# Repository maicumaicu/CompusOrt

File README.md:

# CompusOrt

Este es un proyecto para armar un carro con sensores para detectar si las computadoras estan

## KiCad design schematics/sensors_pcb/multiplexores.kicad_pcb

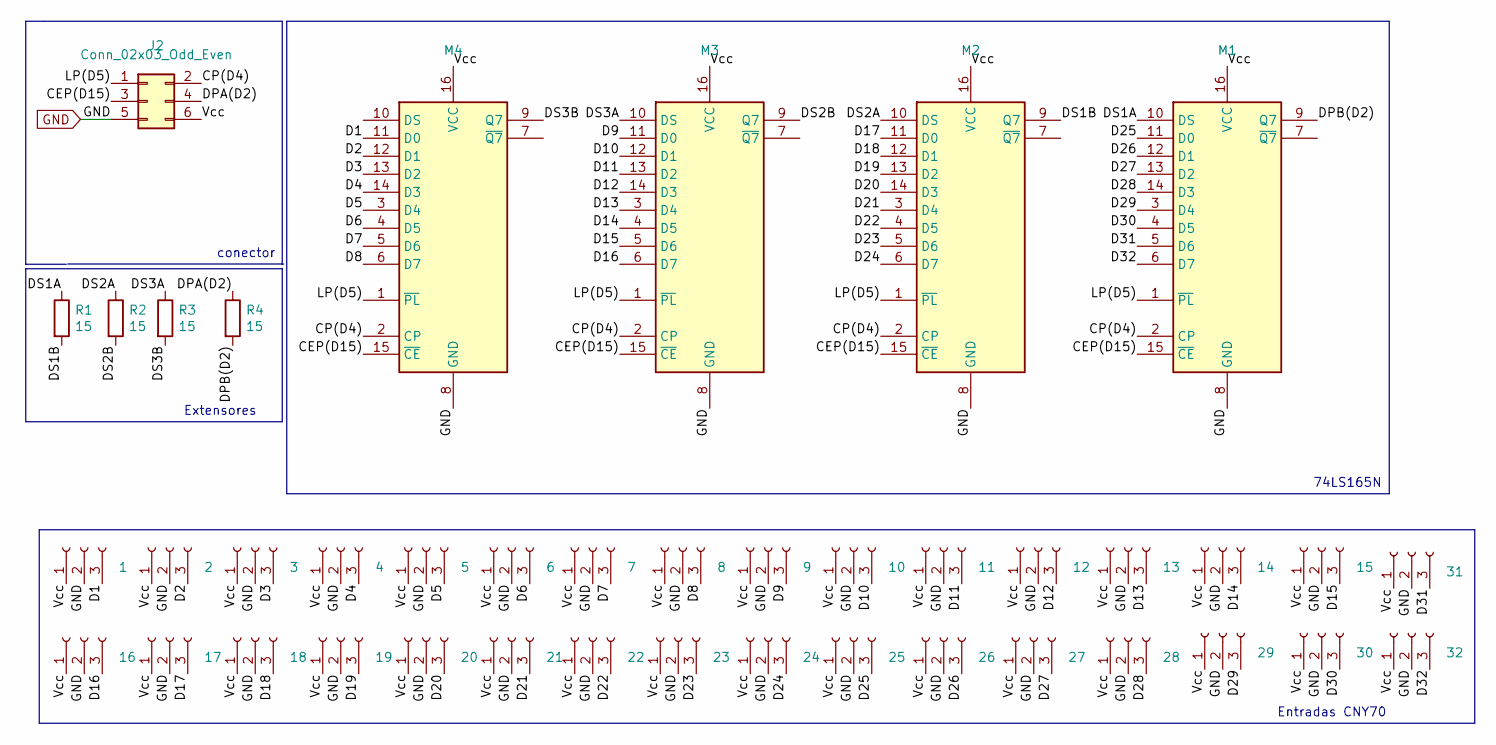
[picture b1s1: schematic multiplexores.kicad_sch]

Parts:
Conn1: 1; PinSocket_1x03_P2.54mm_Vertical
Conn2: 2; PinSocket_1x03_P2.54mm_Vertical
Conn3: 3; PinSocket_1x03_P2.54mm_Vertical
Conn5: 5; PinSocket_1x03_P2.54mm_Vertical
Conn6: 6; PinSocket_1x03_P2.54mm_Vertical
Conn8: 8; PinSocket_1x03_P2.54mm_Vertical
Conn9: 9; PinSocket_1x03_P2.54mm_Vertical
Conn10: 10; PinSocket_1x03_P2.54mm_Vertical
Conn11: 11; PinSocket_1x03_P2.54mm_Vertical
Conn12: 12; PinSocket_1x03_P2.54mm_Vertical
Conn13: 13; PinSocket_1x03_P2.54mm_Vertical
Conn14: 14; PinSocket_1x03_P2.54mm_Vertical
Conn15: 15; PinSocket_1x03_P2.54mm_Vertical
Conn16: 16; PinSocket_1x03_P2.54mm_Vertical
Conn17: 17; PinSocket_1x03_P2.54mm_Vertical
Conn18: 18; PinSocket_1x03_P2.54mm_Vertical
Conn19: 19; PinSocket_1x03_P2.54mm_Vertical
Conn20: 20; PinSocket_1x03_P2.54mm_Vertical
Conn21: 21; PinSocket_1x03_P2.54mm_Vertical
Conn22: 22; PinSocket_1x03_P2.54mm_Vertical
Conn23: 23; PinSocket_1x03_P2.54mm_Vertical
Conn24: 24; PinSocket_1x03_P2.54mm_Vertical
Conn25: 25; PinSocket_1x03_P2.54mm_Vertical
Conn26: 26; PinSocket_1x03_P2.54mm_Vertical
Conn27: 27; PinSocket_1x03_P2.54mm_Vertical
Conn28: 28; PinSocket_1x03_P2.54mm_Vertical
Conn29: 29; PinSocket_1x03_P2.54mm_Vertical
Conn30: 30; PinSocket_1x03_P2.54mm_Vertical
Conn31: 31; PinSocket_1x03_P2.54mm_Vertical
Conn32: 32; PinSocket_1x03_P2.54mm_Vertical
J2: Conn_02x03_Odd_Even; IDC-Header_2x03_P2.54mm_Vertical
M1, M2, M3, M4: 74LS165; DIP-16_W7.62mm_Socket_LongPads
R1, R2, R3, R4: 15; extensor 15mm
conn4: 4; PinSocket_1x03_P2.54mm_Vertical
conn7: 7; PinSocket_1x03_P2.54mm_Vertical

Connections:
/CEP(D15): J2.3, M1.15 (~CE), M2.15 (~CE), M3.15 (~CE), M4.15 (~CE)
/CP(D4): J2.2, M1.2 (CP), M2.2 (CP), M3.2 (CP), M4.2 (CP)
/D1: Conn1.3, M4.11 (D0)
/D2: Conn2.3, M4.12 (D1)
/D3: Conn3.3, M4.13 (D2)
/D4: M4.14 (D3), conn4.3
/D5: Conn5.3, M4.3 (D4)
/D6: Conn6.3, M4.4 (D5)
/D7: M4.5 (D6), conn7.3
/D8: Conn8.3, M4.6 (D7)
/D9: Conn9.3, M3.11 (D0)
/D10: Conn10.3, M3.12 (D1)
/D11: Conn11.3, M3.13 (D2)
/D12: Conn12.3, M3.14 (D3)
/D13: Conn13.3, M3.3 (D4)
/D14: Conn14.3, M3.4 (D5)
/D15: Conn15.3, M3.5 (D6)
/D16: Conn16.3, M3.6 (D7)
/D17: Conn17.3, M2.11 (D0)
/D18: Conn18.3, M2.12 (D1)
/D19: Conn19.3, M2.13 (D2)
/D20: Conn20.3, M2.14 (D3)
/D21: Conn21.3, M2.3 (D4)
/D22: Conn22.3, M2.4 (D5)
/D23: Conn23.3, M2.5 (D6)
/D24: Conn24.3, M2.6 (D7)
/D25: Conn25.3, M1.11 (D0)
/D26: Conn26.3, M1.12 (D1)
/D27: Conn27.3, M1.13 (D2)
/D28: Conn28.3, M1.14 (D3)
/D29: Conn29.3, M1.3 (D4)
/D30: Conn30.3, M1.4 (D5)
/D31: Conn31.3, M1.5 (D6)
/D32: Conn32.3, M1.6 (D7)
/DPA(D2): J2.4, R4.1
/DPB(D2): M1.9 (Q7), R4.2
/DS1A: M1.10 (DS), R1.1
/DS1B: M2.9 (Q7), R1.2
/DS2A: M2.10 (DS), R2.1
/DS2B: M3.9 (Q7), R2.2
/DS3A: M3.10 (DS), R3.1
/DS3B: M4.9 (Q7), R3.2
/LP(D5): J2.1, M1.1 (~PL), M2.1 (~PL), M3.1 (~PL), M4.1 (~PL)
/Vcc: Conn1.1, Conn2.1, Conn3.1, Conn5.1, Conn6.1, Conn8.1, Conn9.1, Conn10.1, Conn11.1, Conn12.1, Conn13.1, Conn14.1, Conn15.1, Conn16.1, Conn17.1, Conn18.1, Conn19.1, Conn20.1, Conn21.1, Conn22.1, Conn23.1, Conn24.1, Conn25.1, Conn26.1, Conn27.1, Conn28.1, Conn29.1, Conn30.1, Conn31.1, Conn32.1, J2.6, M1.16 (VCC), M2.16 (VCC), M3.16 (VCC), M4.16 (VCC), conn4.1, conn7.1
GND: Conn1.2, Conn2.2, Conn3.2, Conn5.2, Conn6.2, Conn8.2, Conn9.2, Conn10.2, Conn11.2, Conn12.2, Conn13.2, Conn14.2, Conn15.2, Conn16.2, Conn17.2, Conn18.2, Conn19.2, Conn20.2, Conn21.2, Conn22.2, Conn23.2, Conn24.2, Conn25.2, Conn26.2, Conn27.2, Conn28.2, Conn29.2, Conn30.2, Conn31.2, Conn32.2, J2.5, M1.8 (GND), M2.8 (GND), M3.8 (GND), M4.8 (GND), conn4.2, conn7.2

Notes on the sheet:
Extensores
Entradas CNY70
74LS165N
conector

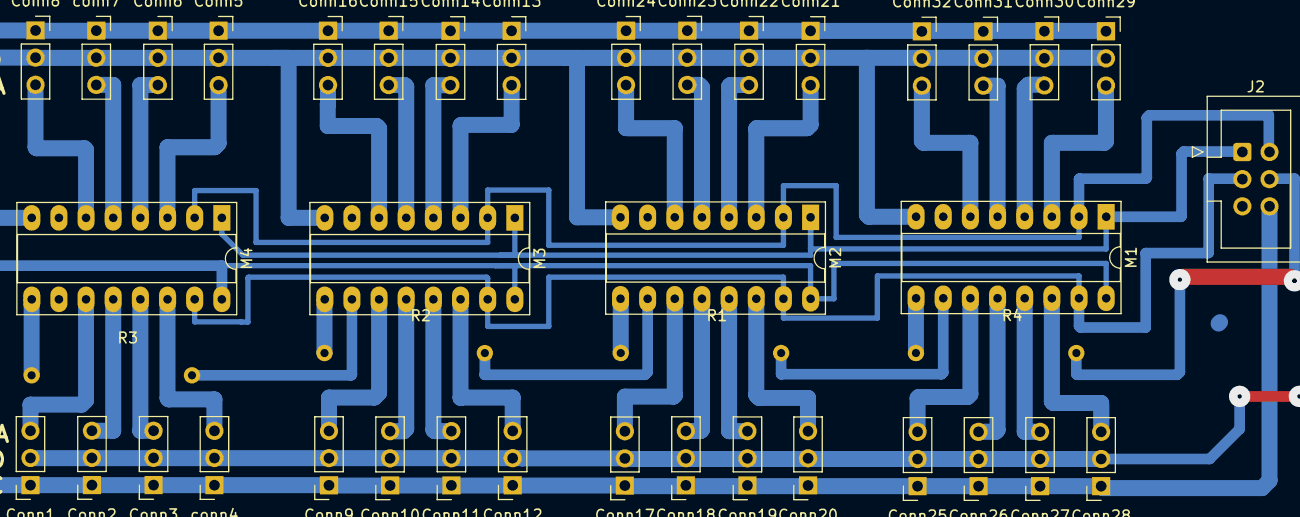
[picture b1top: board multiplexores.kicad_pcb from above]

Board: 2 copper layers, 41 parts (0 on the bottom side), 45 nets.

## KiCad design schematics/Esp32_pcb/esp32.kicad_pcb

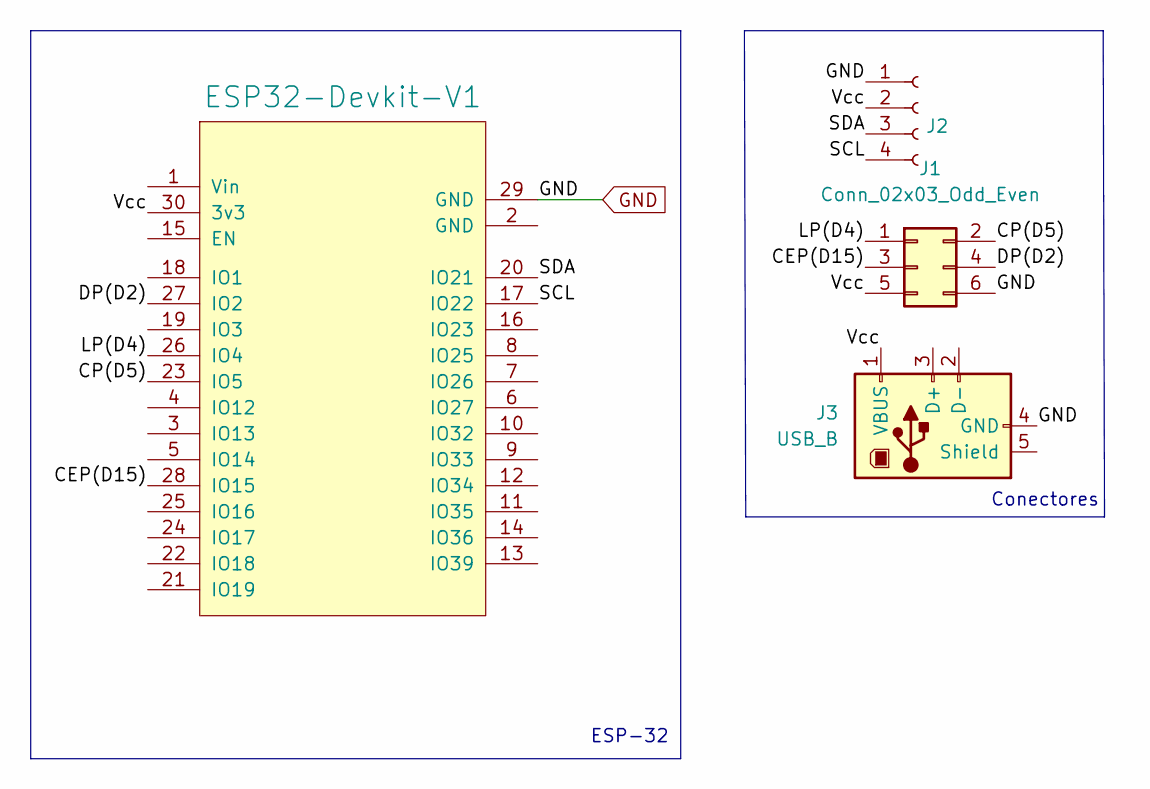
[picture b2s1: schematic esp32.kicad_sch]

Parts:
J1: Conn_02x03_Odd_Even; IDC-Header_2x03_P2.54mm_Vertical
J2: Conn_01x04_Female; PinHeader_1x04_P2.54mm_Vertical
J3: USB_B; USB_B_Lumberg_2411_02_Horizontal
U1: ESP32-Devkit-V1; DOIT_ESP32_Devkit

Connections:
/CEP(D15): J1.3, U1.28 (IO15)
/CP(D5): J1.2, U1.23 (IO5)
/DP(D2): J1.4, U1.27 (IO2)
/LP(D4): J1.1, U1.26 (IO4)
/SCL: J2.4, U1.17 (IO22)
/SDA: J2.3, U1.20 (IO21)
/Vcc: J1.5, J2.2, J3.1 (VBUS), U1.30 (3v3)
GND: J1.6, J2.1, J3.4 (GND), U1.29 (GND)

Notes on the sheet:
Conectores
ESP-32

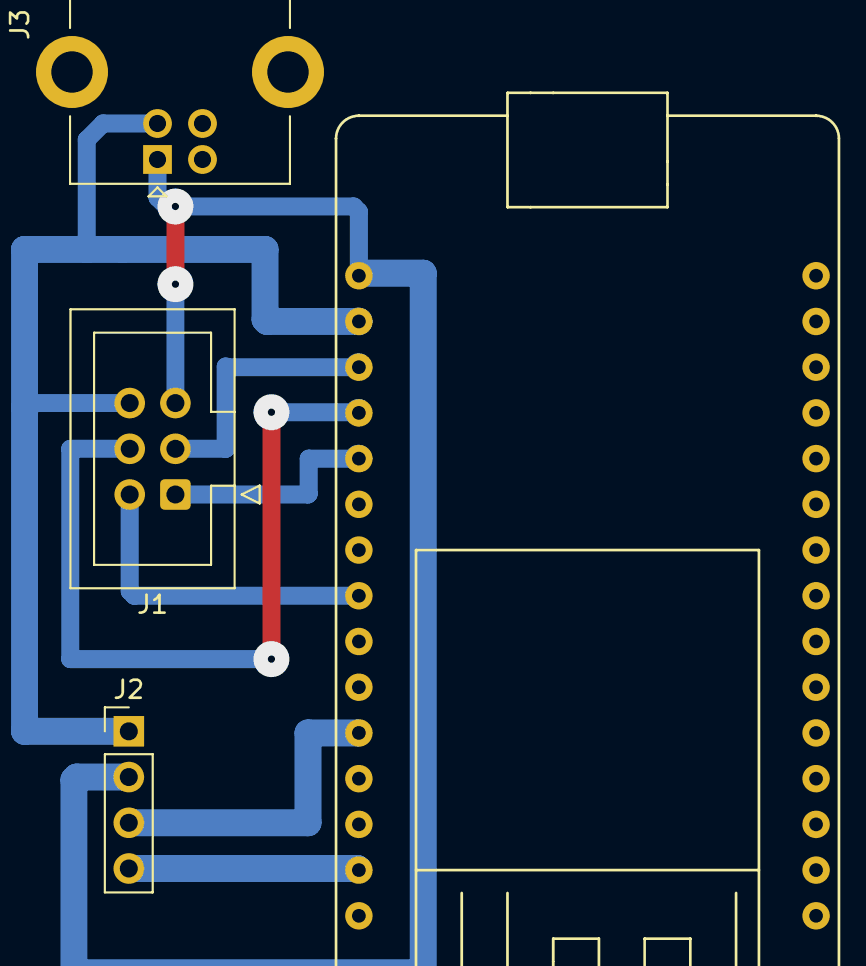
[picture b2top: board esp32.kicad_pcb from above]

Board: 2 copper layers, 4 parts (0 on the bottom side), 8 nets.

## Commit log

2021-07-31 main
2022-05-08 actualizo la placa por completo
2022-05-09 subir
2022-05-13 cambio poligono de gnd
